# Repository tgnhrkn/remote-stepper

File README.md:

# remote-stepper

See blog/intro.md

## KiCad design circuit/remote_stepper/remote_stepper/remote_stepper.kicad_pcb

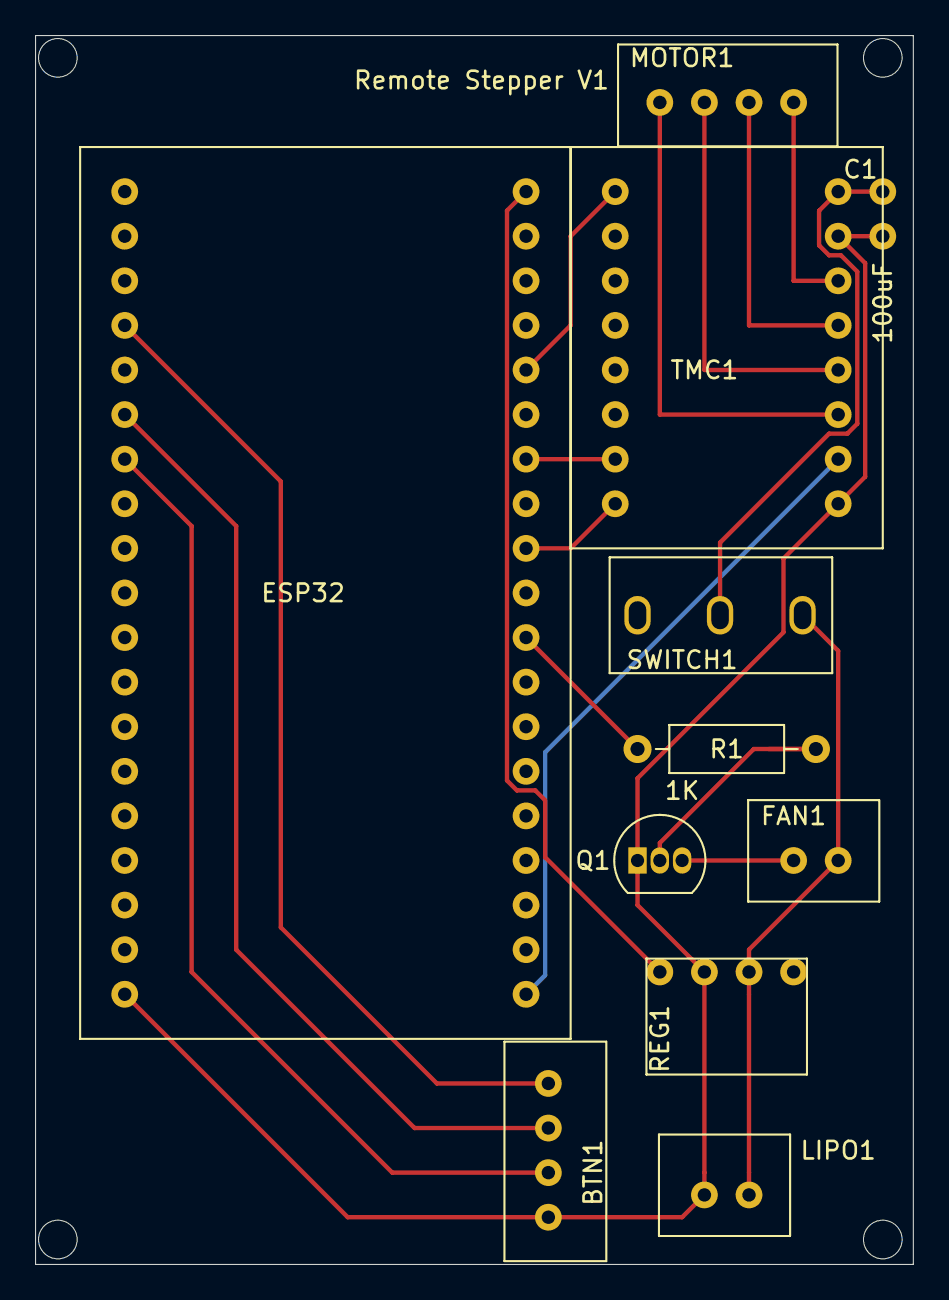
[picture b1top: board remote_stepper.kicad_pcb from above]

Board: 2 copper layers, 50.0 x 70.0 mm, 11 parts (0 on the bottom side), 18 nets.

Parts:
BTN1: button_connector; XH-4A
C1: 100uF; XH-2A
ESP32: teylen_esp_wroom_32; 38pin_2.54mm_pitch_10wide
FAN1: fan_connector; XH-2A
LIPO1: 14.8V Battery; XH-2A
MOTOR1: motor_connector; XH-4A
Q1: PN2222A; TO-92_Inline
R1: 1K; R_Axial_DIN0207_L6.3mm_D2.5mm_P10.16mm_Horizontal
REG1: regulator_100; regulator
SWITCH1: switch
TMC1: TMC2208; tmc2208

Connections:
+3V3: ESP32.20, TMC1.10
+5V: ESP32.38, REG1.1
+BATT: FAN1.1, LIPO1.1, REG1.3, SWITCH1.3
GND: BTN1.1, C1.2, ESP32.19, LIPO1.2, Q1.1, REG1.2, TMC1.9, TMC1.15
unnamed: BTN1.2, ESP32.7
unnamed: BTN1.3, ESP32.6
unnamed: BTN1.4, ESP32.4
unnamed: C1.1, SWITCH1.2, TMC1.16
unnamed: ESP32.28, R1.1
unnamed: ESP32.30, TMC1.8
unnamed: ESP32.32, TMC1.7
unnamed: ESP32.34, TMC1.1
unnamed: FAN1.2, Q1.3
unnamed: MOTOR1.1, TMC1.14
unnamed: MOTOR1.2, TMC1.13
unnamed: MOTOR1.3, TMC1.12
unnamed: MOTOR1.4, TMC1.11
unnamed: Q1.2, R1.2

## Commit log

2022-02-16 add blog and source
2022-03-17 add kicad files
